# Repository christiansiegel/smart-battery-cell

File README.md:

# Arduino-based Smart Battery Cell Research Platform

Accessible smart battery cell research platform based on the Arduino environment. Smart battery cells are a recent research direction in the scope of Battery Management Systems (BMS) for large lithium-ion battery packs, where each battery cell is equipped with an individual Cell Management Unit (CMU). The wireless System on Chip (SOC) solution ESP8266 forms the core of the research platform. It is deployed on an off-the-shelf development board and extended with a custom shield. A single-board computer provides the wireless network for the smart battery cells and acts as gateway to a web service for interaction purposes. As a proof-of-concept, a web client is created that communicates with the battery pack via the MQTT protocol.

## Repository Structure

### cloud
Cloud server running MQTT broker and Webserver. See [setup guide](cloud/README.md) for more details.

### cmu
Cell Management Unit Arduino sketch.

### doc
Documentation comprising a [PDF paper](doc/paper.pdf) and a more detailed [PDF report](doc/report.pdf).

### gateway
Gateway Java code. Also contains a [setup guide](gateway/README.md) for a Raspberry Pi 3.

### schematic
Schematic design files (CadSoft EAGLE) of the smart battery cell.

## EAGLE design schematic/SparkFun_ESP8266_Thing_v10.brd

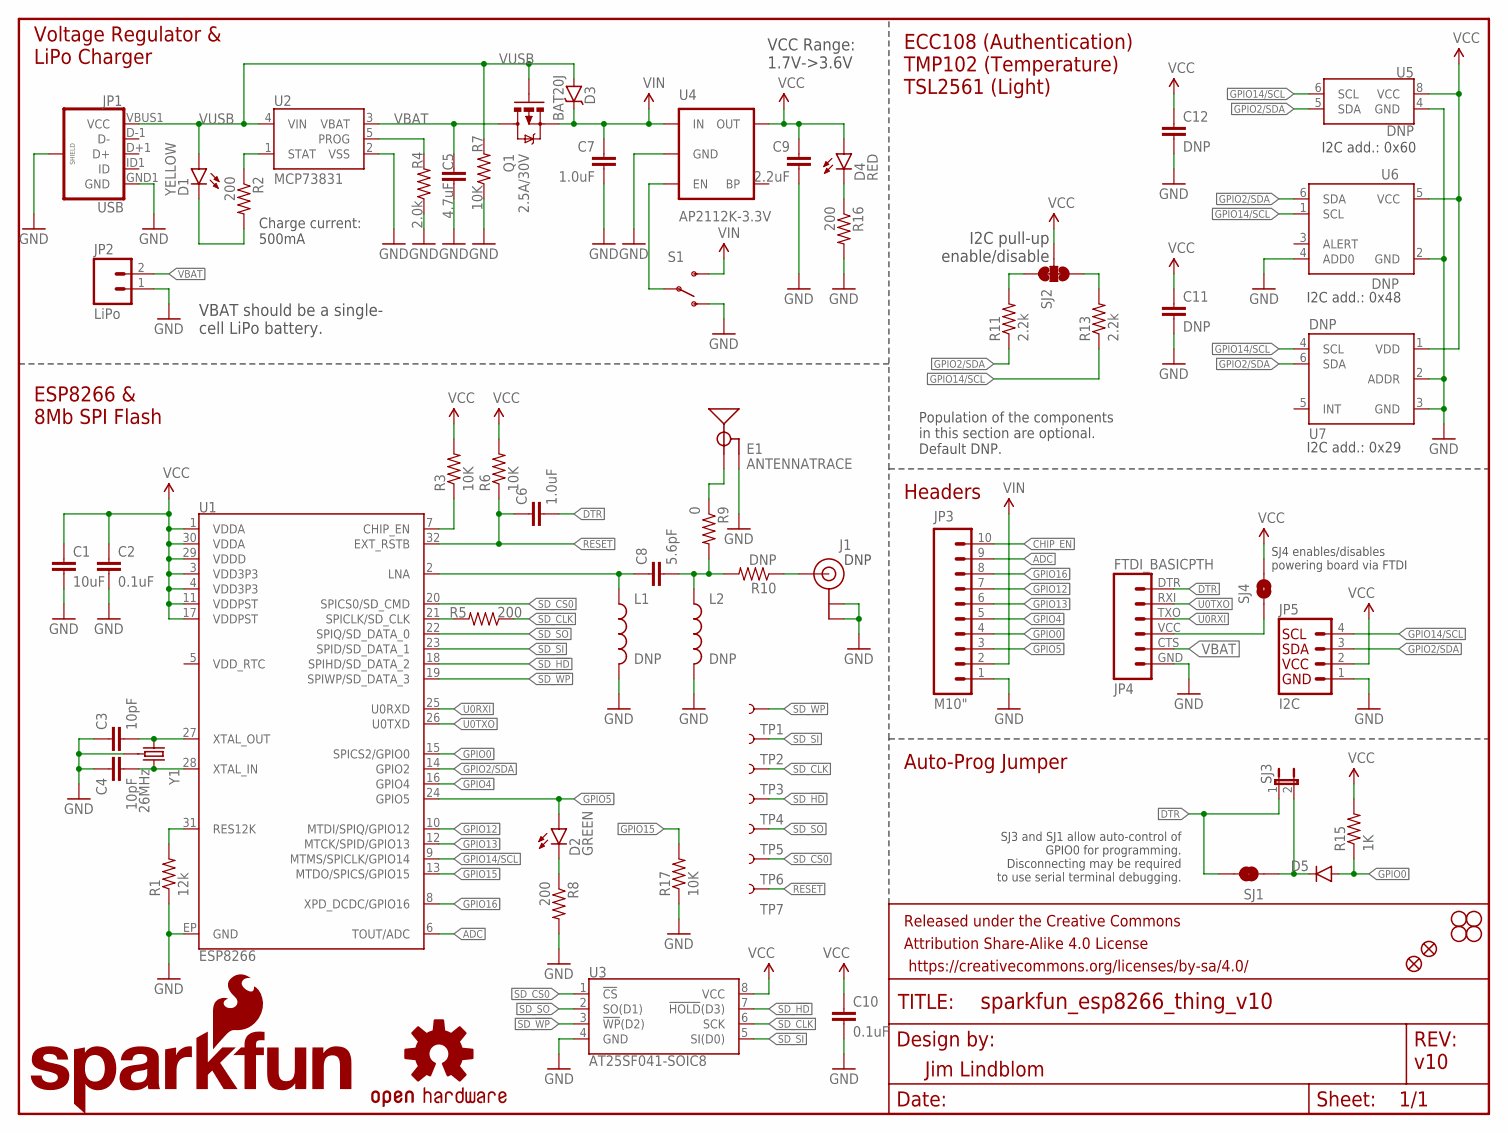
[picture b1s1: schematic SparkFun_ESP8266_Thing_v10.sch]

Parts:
C1: 10uF; 0603-CAP
C2, C10: 0.1uF; 0603-CAP
C3, C4: 10pF; 0603-CAP
C5: 4.7uF; 0603-CAP
C6: 1.0uF; 0603-CAP
C7: 1.0uF; 0805
C8: 5.6pF; 0603-CAP
C9: 2.2uF; 0603-CAP
C11, C12: DNP; 0603-CAP
D1: YELLOW; LED-0603
D2: GREEN; LED-0603
D3: BAT20J; SOD-323
D4: RED; LED-0603
D5: DIODEBAS16; SOD-323
E1: ANTENNATRACE; TRACE_ANTENNA_2.4GHZ_25.7MM
FID1, FID2: FIDUCIAL1X2; FIDUCIAL-1X2
FRAME1: FRAME-LETTER; CREATIVE_COMMONS
J1: DNP; U.FL
JP1: USB; USB-B-MICRO-SMD_V03
JP2: LiPo; JST-2-PTH
JP3: M10"; 1X10
JP4: FTDI_BASICPTH; FTDI_BASIC
JP5: I2C; 1X04
L1, L2: DNP; 0603
LOGO1: SFE_LOGO_NAME.2_INCH; SFE_LOGO_NAME_.2
LOGO3: SFE_LOGO_FLAME.1_INCH; SFE_LOGO_FLAME_.1
LOGO4: OSHW-LOGOS; OSHW-LOGO-S
Q1: 2.5A/30V; SOT23-3
R1: 12k; 0603-RES
R2, R5, R8, R16: 200; 0603-RES
R3, R6, R7, R17: 10K; 0603-RES
R4: 2.0k; 0603-RES
R9: 0; 0603
R10: DNP; 0603-RES
R11, R13: 2.2k; 0603-RES
R15: 1K; 0603-RES
S1: SWITCH-SPDT-SMD-A; SWITCH-SPST-SMD-A
SJ1: JUMPER-PAD-2-NC_BY_TRACE; PAD-JUMPER-2-NC_BY_TRACE_YES_SILK
SJ2: JUMPER-PAD-3-NC_BY_TRACE; PAD-JUMPER-3-3OF3_NC_BY_TRACE_YES_SILK_FULL_BOX
SJ3: JUMPER-PTH-2-NC; PTH-JUMPER-NC_BOTTOM_NO_SILK
SJ4: JUMPER-PAD-2-NOYES_SILK; PAD-JUMPER-2-NO_YES_SILK
STANDOFF1, STANDOFF2, STANDOFF3, STANDOFF4: STAND-OFF
TP1, TP2, TP3, TP4, TP5, TP6, TP7: TEST-POINT3X5; PAD.03X.05
U1: ESP8266; QFN32
U2: MCP73831; SOT23-5
U3: AT25SF041-SOIC8; SO08
U4: AP2112K-3.3V; SOT23-5
U5: DNP; UDFN8
U6: DNP; SOT563-2
U7: DNP; FN-6
Y1: 26MHz; CRYSTAL-SMD-3.2X2.5

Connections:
ADC: JP3.9, U1.6 (TOUT/ADC)
ANT: J1.P$3 (SIGNAL), R10.1
CHIP_EN: JP3.10, R3.1, U1.7 (CHIP_EN)
DTR: C6.2, JP4.DTR (1), SJ1.2, SJ3.1
FTDI_VCC: JP4.VCC (4), SJ4.1
GND: C1.2, C2.2, C3.1, C4.1, C5.2, C7.2, C9.2, C10.2, C11.2, C12.2, E1.GND, E1.GND2 (GND), J1.P$1 (GND), J1.P$2 (GND), JP1.GND1 (GND), JP1.SHIELD1 (SHIELD), JP1.SHIELD2 (SHIELD), JP1.SHIELD3 (SHIELD), JP2.1, JP3.1, JP4.GND (6), JP5.1, L1.2, L2.2, R1.1, R4.1, R7.1, R8.2, R16.2, R17.1, S1.1 (O), U1.EP (GND), U2.2 (VSS), U3.4 (GND), U4.2 (GND), U5.4 (GND), U6.2 (GND), U6.4 (ADD0), U7.2 (ADDR), U7.3 (GND), Y1.2 (GND), Y1.4 (GND)
GPIO0: D5.A, JP3.4, R15.1, U1.15 (SPICS2/GPIO0)
GPIO2/SDA: JP5.3, R11.1, U1.14 (GPIO2), U5.5 (SDA), U6.6 (SDA), U7.6 (SDA)
GPIO4: JP3.5, U1.16 (GPIO4)
GPIO5: D2.A, JP3.3, U1.24 (GPIO5)
GPIO12: JP3.7, U1.10 (MTDI/SPIQ/GPIO12)
GPIO13: JP3.6, U1.12 (MTCK/SPID/GPIO13)
GPIO14/SCL: JP5.4, R13.1, U1.9 (MTMS/SPICLK/GPIO14), U5.6 (SCL), U6.1 (SCL), U7.4 (SCL)
GPIO15: R17.2, U1.13 (MTDO/SPICS/GPIO15)
GPIO16: JP3.8, U1.8 (XPD_DCDC/GPIO16)
LNA: C8.1, L1.1, U1.2 (LNA)
unnamed: R1.2, U1.31 (RES12K)
unnamed: C4.2, U1.28 (XTAL_IN), Y1.3 (2)
unnamed: C3.2, U1.27 (XTAL_OUT), Y1.1
unnamed: D4.C, R16.1
unnamed: C8.2, L2.1, R9.2, R10.2
unnamed: R5.2, U1.21 (SPICLK/SD_CLK)
unnamed: D5.C, SJ1.1, SJ3.2
unnamed: R11.2, SJ2.1
unnamed: R13.2, SJ2.3
unnamed: S1.2, U4.3 (EN)
unnamed: R4.2, U2.5 (PROG)
unnamed: D2.C, R8.1
unnamed: D1.C, R2.2
unnamed: R2.1, U2.1 (STAT)
RESET: C6.1, R6.1, TP7.P$1, U1.32 (EXT_RSTB)
SD_!HD!: TP4.P$1, U1.18 (SPIHD/SD_DATA_2), U3.7 (!HOLD!(D3))
SD_!WP!: TP1.P$1, U1.19 (SPIWP/SD_DATA_3), U3.3 (!WP!(D2))
SD_CLK: R5.1, TP3.P$1, U3.6 (SCK)
SD_CS0: TP6.P$1, U1.20 (SPICS0/SD_CMD), U3.1 (!CS!)
SD_SI: TP2.P$1, U1.23 (SPID/SD_DATA_1), U3.5 (SI(D0))
SD_SO: TP5.P$1, U1.22 (SPIQ/SD_DATA_0), U3.2 (SO(D1))
TRACE_ANT: E1.ANT (SIGNAL), R9.1
U0RXI: JP4.TXO (3), U1.25 (U0RXD)
U0TXO: JP4.RXI (2), U1.26 (U0TXD)
VBAT: C5.1, JP2.2, JP4.CTS (5), Q1.3 (D), U2.3 (VBAT)
VCC: C1.1, C2.1, C9.1, C10.1, C11.1, C12.1, D4.A, JP5.2, R3.2, R6.2, R15.2, SJ2.2, SJ4.2, U1.1 (VDDA), U1.3 (VDD3P3), U1.4 (VDD3P3), U1.11 (VDDPST), U1.17 (VDDPST), U1.29 (VDDD), U1.30 (VDDA), U3.8 (VCC), U4.5 (OUT), U5.8 (VCC), U6.5 (VCC), U7.1 (VDD)
VIN: C7.1, D3.C, JP3.2, Q1.2 (S), S1.3 (S), U4.1 (IN)
VUSB: D1.A, D3.A, JP1.VBUS1 (VCC), Q1.1 (G), R7.2, U2.4 (VIN)

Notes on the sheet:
Jim Lindblom
ECC108 (Authentication) TMP102 (Temperature) TSL2561 (Light)
Voltage Regulator & LiPo Charger
ESP8266 & 8Mb SPI Flash
Headers
Auto-Prog Jumper
v10
VCC Range: 1.7V->3.6V
VBAT should be a single- cell LiPo battery.
I2C pull-up enable/disable
SJ4 enables/disables powering board via FTDI
SJ3 and SJ1 allow auto-control of GPIO0 for programming. Disconnecting may be required to use serial terminal debugging.
I2C add.: 0x48
I2C add.: 0x60
I2C add.: 0x29
Population of the components in this section are optional. Default DNP.
Charge current: 500mA
DNP

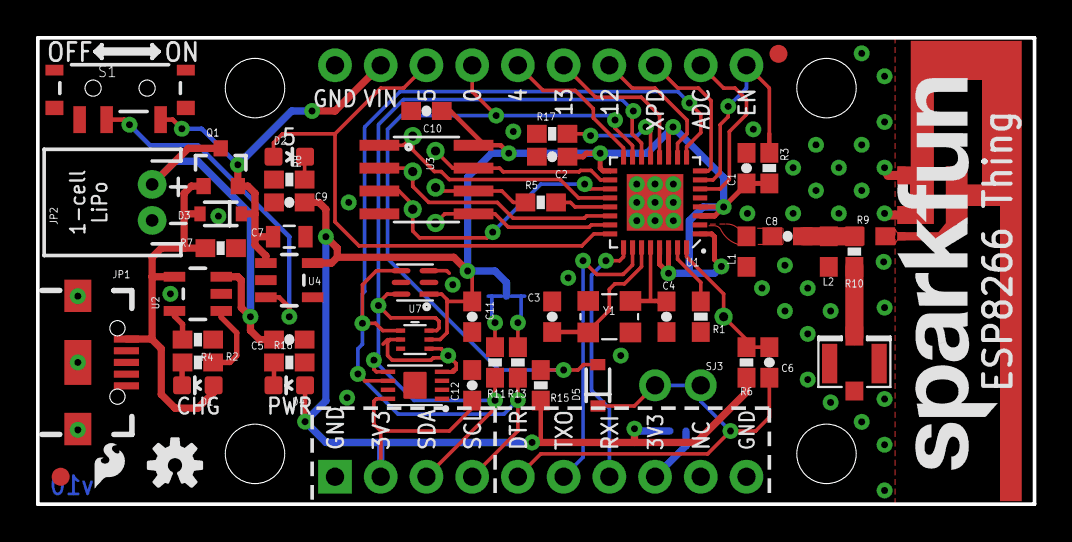
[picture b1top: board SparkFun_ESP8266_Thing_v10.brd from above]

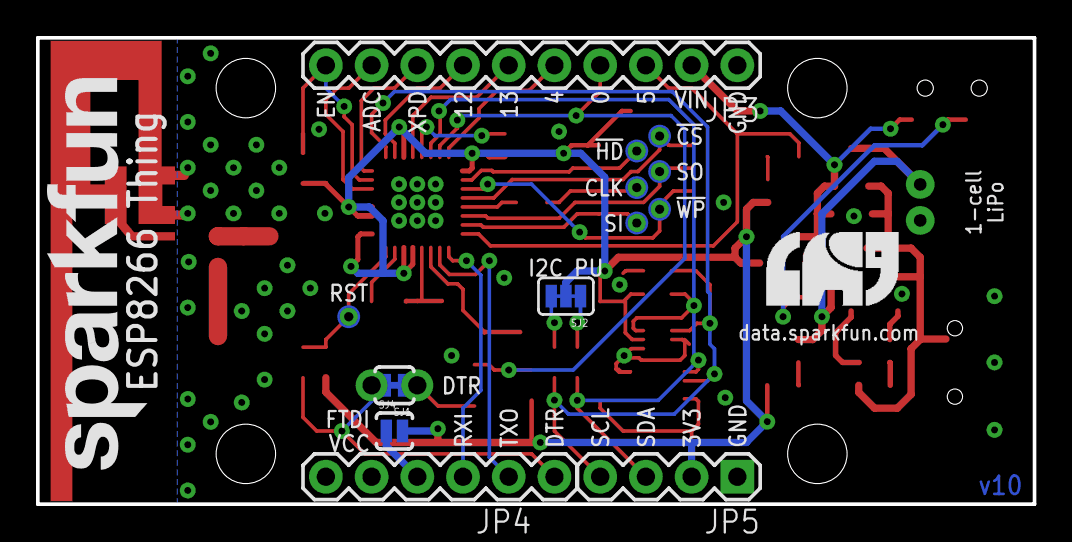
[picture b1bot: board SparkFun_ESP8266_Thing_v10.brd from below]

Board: 2 copper layers, 55.4 x 25.9 mm, 73 parts (14 on the bottom side), 44 nets.

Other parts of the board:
LOGO5: SFE_LOGO_NAME.2_INCH; SFE_LOGO_NAME_.2

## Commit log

2017-07-28 added missing newlines
2017-07-28 reduce image size
2017-07-28 use img tag with width

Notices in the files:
parts and their libraries:
SparkFun-Capacitors: Licensing: Creative Commons ShareAlike 4.0 International - https://creativecommons.org/licenses/by-sa/4.0
SparkFun-Aesthetics: Released under the Creative Commons Attribution Share-Alike 4.0 License
SparkFun-Aesthetics: https://creativecommons.org/licenses/by-sa/4.0
